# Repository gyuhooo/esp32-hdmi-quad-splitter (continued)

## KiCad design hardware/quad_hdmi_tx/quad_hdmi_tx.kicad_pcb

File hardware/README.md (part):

# 基板 (2 枚構成)

| 基板 | 内容 | 詳細 |
|---|---|---|
| `quad_hdmi_tx/` キャリア基板 rev B | ADV7513 ×4 + TPD12S016 ×4 + HDMI ×4、115 × 38 mm、6 層。裏面に 2×40 ヘッダ J7/J8 | この README |
| `fpga_main/` FPGA メイン基板 rev A | XC7A35T-1FTG256C、QSPI フラッシュ、JTAG、100 MHz、電源(5 V → 1.0 / 1.8 / 3.3 V)、115 × 72 mm、6 層。表面の 2×40 ソケット J1/J2 にキャリアを重ねる | [fpga_main/README.md](fpga_main/README.md) |

キャリア基板はメイン基板の上に重ね(基板間 約 11 mm、M3 スペーサ)、124 本の 3.3 V 信号 + GND + FPGA_5V をソケットで直結する。
両基板の KiCad プロジェクトは `gen/` のスクリプトが生成する(回路図 → ネットリスト → 配置と事前配線 → FreeRouting → DRC → ガーバー)。
FPGA のピン割り当て(`fpga_main/fpga_pinmap.csv`)から `gen/gen_xdc.py` が `constraints/board.xdc` を作る。

# Quad HDMI TX キャリア基板 (ADV7513 ×4)

FPGA メイン基板(下記 `fpga_main/`)から 24bit RGB ×4 を受け、HDMI 4 本を出す基板の KiCad 7 プロジェクト。
`gen/gen_schematic.py` が回路図・BOM・ピン割り当て表を生成し、`kicad-cli` でネットリストと PDF を書き出している。

| ファイル | 内容 |
|---|---|
| quad_hdmi_tx/quad_hdmi_tx.kicad_pro / *.kicad_sch | KiCad 7 プロジェクト(ルート + 電源 + FPGA コネクタ + HDMI OUT1〜4) |
| quad_hdmi_tx/quad_hdmi_tx.pdf | 回路図 PDF(7 ページ) |
| quad_hdmi_tx/netlist.net | kicad-cli で書き出したネットリスト |
| quad_hdmi_tx/bom.csv, bom_grouped.csv | 部品表(リファレンス別 / 集計、MPN 付き) |
| quad_hdmi_tx/fpga_header_pinmap.csv | J7/J8 のピン → 信号名 → FPGA メイン基板のボール(`gen/fpga_common.py` の割り当てで自動記入) |
| quad_hdmi_tx/quad_hdmi_tx.kicad_pcb | 基板レイアウト rev B(6 層、115 × 38 mm の細長い基板)。`gen/gen_pcb.py` が配置・プレーン・事前配線を生成し、FreeRouting で自動配線 |
| quad_hdmi_tx/drc.rpt | DRC レポート(pcbnew API) |
| quad_hdmi_tx/fab/ | ガーバー、ドリル、CPL(部品座標)、各層の PDF(`gen/export_fab.sh`) |
| quad_hdmi_tx/3d/ | STEP(基板のみ)、簡易 3D モデル(OBJ + テクスチャ)、three.js ビューア(`gen/gen_3d.py`、`gen/make_3d_textures.py`) |
| gen/ | 生成スクリプト(両基板)、ネットリスト検査、配線パイプライン。`sch_common.py`(回路図共通部)、`fpga_common.py`(FPGA のボール割り当て) |

## 回路構成

```
USB-C 5V ─ F1(PTC 2A) ─ +5V ─ U5 AP63203 (3.3V 2A buck) ─ +3V3 ─┬─ U13 TLV1117LV18 ─ CH1_1V8 ─ U11 ADV7513 ─ U12 TPD12S016 ─ J1 HDMI
                                                               ├─ U23 ...                          CH2 (I2C bus A, addr 0x7A)
                                                               ├─ U33 ...                          CH3 (I2C bus B, addr 0x72)
                                                               └─ U43 ...                          CH4 (I2C bus B, addr 0x7A)
J7 / J8 (2×40 SMD、裏面): 各チャネル 20 ピンずつ。J7 = D13-23 + D1/D2/D4/D5/D10、J8 = D0/D3/D6-9/D11/D12, CLK, DE/HS/VS, HPD, INT (+ I2C_A/I2C_B, FPGA_5V)
```

### チャネル(×4)

| 要素 | 内容 | 根拠 |
|---|---|---|
| ADV7513BSWZ (LQFP-64 EP) | 24bit RGB 4:4:4 入力 ID 0、セパレートシンク。TMDS 出力 | データシート Rev.B Table 3 のピン配置 |
| R_EXT 887 Ω 1% | TMDS 基準電流 | データシート Table 3 |
| PD/AD 10 kΩ | GND → I2C 0x72(7bit 0x39)、+3V3 → 0x7A(0x3D)。同一バス 2 台をこれで分ける | |
| INT 10 kΩ プルアップ | ヘッダへ | |
| CEC_CLK 0 Ω→GND | CEC 未使用。使う場合は 0 Ω を外して 3〜100 MHz を入れる | Table 3 |
| 未使用オーディオ入力 | SPDIF, MCLK, I2S0-3, SCLK, LRCLK を GND | |
| 電源 | DVDD ×4 / AVDD ×3 / PVDD / BGVDD = 1.8 V、DVDD_3V = 3.3 V。1.8 V はチャネルごとの LDO。AVDD と PVDD/BGVDD はフェライトビーズ経由 | 1.8 V 系は最大 256 mW/個 |
| TPD12S016PWR (TSSOP-24) | TMDS 8 本の ESD、DDC/CEC のレベルシフト(A 側 3.3 V、B 側 5 V プルアップ内蔵)、HPD、5V_OUT(55 mA リミット) | データシート SLLSE96F |
| LS_OE / CT_HPD | +3V3 固定(常時有効) | |
| HDMI A(Molex 208658-1001) | シールド、GND、SH は GND。UTILITY(14) は未接続 | |

### 電源

- USB-C(GCT USB4105-GF-A、USB2.0 16P)、CC1/CC2 に 5.1 kΩ(5 V 3 A シンク宣言)。代替 5 V 入力 J6。
- F1: PTC 2 A。+5V と VBUS に PWR_FLAG。
- U5 AP63203WU(3.3 V 固定、2 A): CIN 10 µF ×2、CBST 0.1 µF、L 4.7 µH(NR4018T4R7M)、COUT 22 µF ×2、EN は 100 kΩ で VIN へ。
- 消費見積: 1.8 V 系 4 × 142 mA ≈ 0.57 A(LDO 損失 ≈ 0.85 W、SOT-223 ×4 に分散)、3.3 V 系合計 ≈ 0.7 A、5 V 入力 ≈ 0.8 A(HDMI 5V_OUT 4 × 55 mA 含む)。
- JP1(ソルダージャンパ)を閉じると J8 の 39-40 ピン(FPGA_5V)から FPGA ボードへ 5 V を供給できる。FPGA ボードが自前電源のときは開けたままにする。

### FPGA コネクタ J7 / J8

- 2×40 ピン 2.54 mm の SMD ヘッダ 2 本を **裏面** に長辺と平行に置く(Samtec TSM-140-01-L-DV 相当)。リボンケーブル(IDC)で FPGA ボードへ。
- ヘッダの列 k(ピン 2k-1 / 2k)は OUT ⌈k/10⌉ の ADV7513 の真下にある。各チャネルは J7 で 20 ピン(ADV 左辺の D13-23 と下辺の D1/D2/D4/D5/D10、GND ×4)、J8 で 20 ピン(ADV 下辺の D0/D3/D6-9/D11、CLK, DE/HS と D12、VS, HPD, INT、GND ×4、OUT1/OUT3 は I2C、OUT2 は FPGA_5V ×2)。
  データ線の並びは配線経路(内層の通路の順序)で決めたもので、ビット順ではない。FPGA 側のピン割り当ては `fpga_header_pinmap.csv` を参照。
- GND は ADV / TPD の真下の列(J7 列 4-7 下段、J8 列 4-7 上段)に置いている(表面がふさがっていて信号のビアが打てない位置)。リボンケーブル上では 4〜9 本おき。ケーブルは 15 cm 以下を推奨(148.5 MHz SDR)。
- 3.3 V LVCMOS。FPGA ボードの該当バンクは VCCO = 3.3 V であること。
- スタック高さは 30 mm 以下を推奨(148.5 MHz SDR)。FPGA 側で 22〜33 Ω の直列終端を入れられるとなお良い。
- 相手は FPGA メイン基板 `fpga_main/` のソケット J1(= J7)/ J2(= J8)。FPGA ピンは `fpga_main/fpga_pinmap.csv` と `fpga_header_pinmap.csv` の FPGA_pin 列にあり、`python3 gen/gen_xdc.py > constraints/board.xdc` で XDC を作る。
- 市販 FPGA ボードにリボンケーブルで繋ぐ場合は `fpga_header_pinmap.csv` の FPGA_pin 列を書き換えて `gen/gen_xdc.py quad_hdmi_tx/fpga_header_pinmap.csv` を使う。

## 検証状況

| 項目 | 状態 |
|---|---|
| ADV7513 の全 65 ピン、TPD12S016 の全 24 ピンがデータシートどおりに割り当てられている | 済(スクリプトで番号を生成、検査で全ピンの接続を確認) |
| kicad-cli によるネットリスト書き出し | 済(147 部品、233 ネット) |
| ネット検査: データ線 2 ピン、TMDS 3 ピン、HPD/INT 3 ピン、I2C 4 ピン、GND/+3V3 に信号ピンが混ざっていない | 済(`gen/check_netlist.py`) |
| 基板レイアウト(配置・配線) | 済(rev B: 6 層 115 × 38 mm、配線 2010 本、ビア 634 個。HDMI・USB-C コネクタは基板端に合わせ済み) |
| DRC(pcbnew API、KiCad 7 の既定ルール + 本基板のルール) | 未接続 0、クリアランス / 穴 / 外形 / コートヤード違反 0(残りは `lib_footprint_issues` 147 件 = 生成したフットプリントがライブラリと一致しないという情報のみ) |
| TMDS 8 本 × 4 ch | ビアなし、ペア内長差 0.47 mm 以下(スクリプトで固定配線) |
| ガーバー / ドリル / CPL 出力 | 済(`quad_hdmi_tx/fab/`) |
| KiCad GUI での ERC / DRC 再確認 | **未**(GUI で開いて再実行を推奨) |
| 実機評価 | **未** |

### レイアウトの結果

| 層 | 画像 |
|---|---|
| 表面 (F.Cu) |  |
| 裏面 (B.Cu、ミラー表示) |  |
| 内層 1 (GND) |  |
| 内層 2 (SIG1) |  |
| 内層 3 (SIG2) |  |
| 内層 4 (+3V3 / CHn_1V8) |  |

TMDS の事前配線(OUT1 周辺、配線前の状態):

自動配線(FreeRouting 1.9)後の主なネット長:

```
RGB バス / 同期 (112 本): 最長 51.3 mm (D16、ヘッダ上の横レーン経由)、平均 21.4 mm、最短 4.2 mm。すべて gen_pcb.py の固定配線 (ビア 1〜2 個)
I2C_A_SCL 70 mm (OUT1/OUT2 の ADV とプルアップ、J8 経由)、I2C_B_SCL 56 mm
HPD 20 mm、INT 25 mm、DDC_SCL / CEC 15 mm (TPD -> HDMI)、FPGA_5V 72 mm (J8 ピン 39/40 -> JP1)
+5V 197 mm (ビア 9)、+3V3 132 mm (ビア 41、内層 4 のプレーンが主)、GND 326 mm (ビア 203、内層 1 のプレーンが主)
TMDS: ペア内長差 0.05〜0.47 mm、ビアなし
```

### 3D モデル

| 表 | 裏 |
|---|---|
|  |  |

`quad_hdmi_tx/3d/` に 3 種類ある(`gen/gen_3d.py` と `gen/make_3d_textures.py` で生成):

| ファイル | 内容 |
|---|---|
| `quad_hdmi_tx.step` | kicad-cli の STEP 出力。この環境には KiCad の 3D モデルライブラリが無いため **基板のみ**(部品なし)。筐体設計の基準に使える |
| `quad_hdmi_tx_simplified.obj` / `.mtl` / `tex_top.png` / `tex_bot.png` | 簡易モデル(Wavefront OBJ、mm、Y 上)。基板は表裏にレジスト・金パッド・シルクのテクスチャ、部品はパッケージ種別の寸法表による直方体(IC・受動部品・コネクタ・ヘッダのピン) |
| `viewer.html` | 上の簡易モデルを three.js で回転表示する 1 ファイルのビューア(ブラウザで開く) |

部品の外形は寸法表の近似なので、正確な 3D モデルが要るときは KiCad の 3D ライブラリを入れて `kicad-cli pcb export step` を再実行する。

## 発注前チェックリスト

1. **ADV7513 の推奨回路**: ハードウェアユーザーガイド(ADI)で、PVDD/BGVDD のフィルタ構成と HPD/DDC の扱いが本回路(フェライトビーズ + 0.1 µF、TPD12S016 経由)と矛盾しないか確認する。
2. **フットプリント**: ADV7513 の露出パッドは 5.3 mm 角。`LQFP-64-1EP_10x10mm_P0.5mm_EP5x5mm` を使い、EP のサーマルビア(0.5/0.3 mm ×14)は裏面ヘッダのパッドを避けて `gen_pcb.py` が打っている。
3. **HDMI コネクタ**: Molex 208658-1001 の KiCad 標準フットプリント。別品番なら 1〜19 + シェルの配列を照合する。
4. **USB-C**: GCT USB4105-GF-A の標準フットプリント。NPTH と自身のパッドの間隔が 0.194 mm なので、穴クリアランスの規則を 0.18 mm にしている。
5. **LDO**: TLV1117LV18DCYR(セラミック出力対応、1 A)。AMS1117-1.8 はピン互換だがタンタル出力推奨。
6. **I2C アドレス**: 同一バスに 2 台(0x72 と 0x7A)。HDL の `top.v` はバス 0 = OUT1/OUT2、バス 1 = OUT3/OUT4 でこの割り当てを前提にしている。
7. **KiCad GUI で ERC と DRC を再実行する**: 本リポジトリの検査は pcbnew API のレポート。DRC の残り 143 件は「フットプリントがライブラリと一致しない」情報(ライブラリ名なしで読み込んだため)で、製造には影響しない。
8. **インピーダンス**: TMDS は 0.15 mm 幅 / 0.15 mm 間隔で固定配線している。製造業者の 6 層スタックアップ(例: JLC06161H-3313、F.Cu〜In1 が 0.1 mm 程度)の計算値に合わせて幅・間隔を調整し、必要なら `gen/gen_pcb.py` のネットクラスと事前配線幅を変えて再生成する。
9. **自動配線部の目視確認**: RGB バス(148.5 MHz)30 本は `gen_pcb.py` の固定配線(内層 SIG1/SIG2、各線 40 mm 以下)。電源・I2C・CEC・HPD 系は FreeRouting の結果なので、ADV 右辺付近の AVDD/PVDD と I2C の引き回しをレビューし、必要なら手で整える。
10. **シルク**: 参照記号は F.Fab に置いている(シルクには出ない)。実装は `fab/cpl.csv` の座標で行う。
11. **コネクタの基板端合わせ**: HDMI(Molex 208658)と USB-C(GCT USB4105)のフットプリントには "PCB Edge" の基準線がある。
    生成スクリプトはこの線が基板外形(HDMI: y=0、USB-C: x=115)に一致するよう配置している(HDMI は本体が 1.5 mm、USB-C は 0.5 mm 外形からはみ出す)。
    ケースに入れる場合はこのはみ出し量を前提に開口を設計する。
12. **裏面のヘッダと IDC ソケット**: J7/J8 の中心間隔は 15.4 mm、J8 は下辺から 4.4 mm。IDC ソケット(幅 8.9 mm)は J8 側が基板端とほぼ面一になる。基板の下に高さ 10 mm 以上の空間が必要。
13. **両面実装**: LDO ×4、そのコンデンサ、ヘッダ 2 本、JP1 が裏面。実装業者には両面(F+B)の CPL を渡す。裏面の SMD ヘッダはリフロー可能品(TSM-140-01-L-DV 等)を選ぶ。
14. **取付穴**: M3 ×4(HDMI の間に 3 個、右下に 1 個)。HDMI の間の穴はプラグのオーバーモールド(幅 ~21 mm)と干渉しない位置だが、ナットは基板の裏側に置くこと。

## 基板レイアウト

### 配置(rev B: 115 × 38 mm、縦横比 0.33)

```
 y=0  ┌───────────────────────────────────────────────────────────────────────┐
      │ [J1 HDMI] H1 [J2 HDMI]  H2 [J3 HDMI]  H4 [J4 HDMI]   R5 R6 F1  [J5]   │  上辺: HDMI ×4 (25.4 mm ピッチ、開口部は上)。裏面の真裏に LDO
      │  U12 TPD     U22 TPD       U32 TPD       U42 TPD      C54     USB-C   │  TPD12S016 (rot 90)。両脇に +3V3 / 5V 系のコンデンサ
      │  U11 ADV     U21 ADV       U31 ADV       U41 ADV      U5  C51  L1     │  ADV7513 (rot 180)。左右の列に 1V8 / AVDD / PVDD 系
      │                                                      C52 C53  C55 C56 │  電源部 (右端)
 y=38 └───────────────────────────────────────────────────────────────────────┘
        x=0                              裏面: J7 (y=18.2) と J8 (y=33.6) が x=1.6..101.6 に横たわる        x=115

 裏面 (透視): [LDO U13][LDO U23][LDO U33][LDO U43] ← HDMI のシェルタブの穴の間
             ═══════════ J7 2×40 (列 1-10 = OUT1, 11-20 = OUT2, 21-30 = OUT3, 31-40 = OUT4) ═══════════
             ═══════════ J8 2×40 (同じ列割り) ═══════════════════════════════════════════════════  JP1
```

- HDMI 4 個の横幅(4 × 25.4 mm)に電源部を足した 115 mm を横幅とし、縦幅は 38 mm(横の 1/3 以下)。
- 各チャネルは幅 25.4 mm = ヘッダ 10 列。ヘッダの列は ADV の真下なので、RGB バスの配線は 1 本あたり 15 mm 以下。
- TMDS の並び順が ADV7513(rot 180)→ TPD12S016(rot 90)→ HDMI(rot 90)で **交差なし**に揃うよう向きを決めている
  (ADV 上辺: TX2+ TX2- TX1+ TX1- TX0+ TX0- TXC+ TXC-、TPD 上辺: D2+ D2- D1+ D1- D0+ D0- CLK+ CLK-、コネクタ: 1 3 4 6 7 9 10 12)。
- 裏面ヘッダのパッド(1.0 mm 幅、2.54 mm ピッチ)の隙間は 1.54 mm しかないので、貫通ビアはパッド列の隙間の中心(x = cx ± 2.54 m)か、
  2 列の間 / J7-J8 の間の帯に置く。2 端子部品はすべて縦置きでこの x に載せ、外向きのビアが隙間に来るようにしている。
  TPD の A 側ピンのビア(y = 18.3 / 18.7)は J7 の 2 列の隙間(y 17.25〜19.15)に、ADV 上辺の囲われたピンのビア(y = 26.0 / 26.6)は J7-J8 の間の帯に入る。
- ADV のデータピンはルータ任せでは半分が配線できない(裏面ヘッダのパッドが B.Cu を塞ぐ)ので、`gen_pcb.py` が 30 本の RGB/同期/制御線をすべて事前配線する(残りの電源・I2C・CEC などが FreeRouting):
  - 下辺 16 ピンのエスケープビアは本体下(EP とパッド内端の間 = J8 の 2 列の隙間に当たる y)に 2 段。真下の J8 下段 4 本(D11/D8/D3/HS)は裏面で直落とし、
    D6/D7/CLK/D9 と DE/D0 は SIG2 の横レーン(y = 34.8〜36.5)で J8 列 1-2 / 列 9 の隙間ビアへ、D1/D2/D4/D5/D10 は ADV 右脇の通路(x = cx+3.35/3.65/3.95)を上って J7 列 8-10 へ。
  - 左辺 16 ピンは左へ(上 5 本は x=cx-7.0/-7.62 に交互、中 8 本は隙間の列 x=cx-7.62 に 0.65 ピッチで斜めに、D14/D13 は本体下、D12 は隙間の列の一番下)。
    D16-D23 と DDC は左の内層通路(x = cx-8.19〜-9.69、SIG1/SIG2 各 6 レーン)を上り、J7 列 1-2 の隙間ビア、またはヘッダの上(y = 11.5〜12.1)の横レーン経由で列 5-8 上段へ。
    D13/D14/D15 は ADV 脇の帯(x = cx-6.5〜-5.5)を SIG2 で上って列 3-4 へ。J8 列 4-7 上段(GND)は EP のサーマルビアに裏面で直結。
  - レーンの割り当ては「右の通路ほど低い横レーン」「横レーンから下に曲がる先は左ほど低いレーン」の規則で決め、事前配線どうしが交差しないようにしている。
  - そのほか、ルータが落としやすい DDC_SCL(TPD → HDMI、SIG2 で右上へ抜けて表面でコネクタの上を回る)と FPGA_5V(J8 ピン 39/40 → JP1、SIG2 で基板下端を右へ)も固定配線。
- LDO(SOT-223)は HDMI コネクタの真裏、シェルタブの穴の間。出力は裏面の太い配線で内層 4 の 1V8 の島の「首」へ入る。
- 電源部は右端(USB-C の開口部は右)。

### 層構成(6 層、1.6 mm)

| 層 | 用途 |
|---|---|
| F.Cu | 信号(TMDS 事前配線、短い引き出し)、部品 |
| In1.Cu (GND) | GND プレーン(全面) |
| In2.Cu (SIG1) / In3.Cu (SIG2) | 信号(RGB バス、制御線、+5V) |
| In4.Cu (PWR) | +3V3 プレーン。各 ADV の周囲は CHn_1V8 の島(優先度 1)。島は LDO へ向けて首を伸ばしている |
| B.Cu | FPGA ヘッダ、LDO、信号、配線後に GND ベタ |

4 層では裏面ヘッダのパッド列が B.Cu を塞ぐため、RGB バスの配線が成立しない。6 層にして内層 2 層を信号に使う。

### ルール

| 項目 | 値 |
|---|---|
| クリアランス | 0.15 mm |
| 配線幅 | 0.2 mm(TMDS 0.15、Power 0.5) |
| ビア | 0.6/0.3 mm(TMDS・アクセスビア 0.5/0.3、Power 0.8/0.4) |
| 差動 | 100 Ω 目標、0.15/0.15 mm(**製造業者のインピーダンス計算で要調整**) |

### 生成と配線のパイプライン

```
cd hardware/gen
python3 gen_pcb.py                       # 配置・外形・プレーン・事前配線・ファンアウト -> quad_hdmi_tx.kicad_pcb, drc_pre.rpt
python3 route_pcb.py export              # quad_hdmi_tx.dsn
xvfb-run -a java -jar freerouting-1.9.0.jar -de ../quad_hdmi_tx/quad_hdmi_tx.dsn -do ../quad_hdmi_tx/quad_hdmi_tx.ses -mp 24 -oit 1.0   # 約 10 分
python3 route_pcb.py import              # SES 取り込み、外層 GND ベタ、ゾーン塗り、DRC -> drc.rpt
python3 layout_report.py                 # 配線長、ビア数、TMDS ペア長差、DRC 集計
./export_fab.sh                          # fab/ にガーバー・ドリル・CPL・PDF
python3 render_images.py                 # fab/*.pdf → docs/images/pcb-*.png (Pillow, pdftoppm)
python3 gen_3d.py                        # 3d/board3d.json, 簡易 OBJ/MTL (pcbnew)
python make_3d_textures.py               # 3d/tex_*.png と 3d/viewer.html (Pillow + numpy。先に各層の白黒 PDF→PNG が要る、スクリプト冒頭参照)
```

FreeRouting を使う上での注意(実測で判明したもの):

- 外層のベタを DSN に含めると障害物として扱われ配線できないため、ベタは SES 取り込み後に追加している。
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
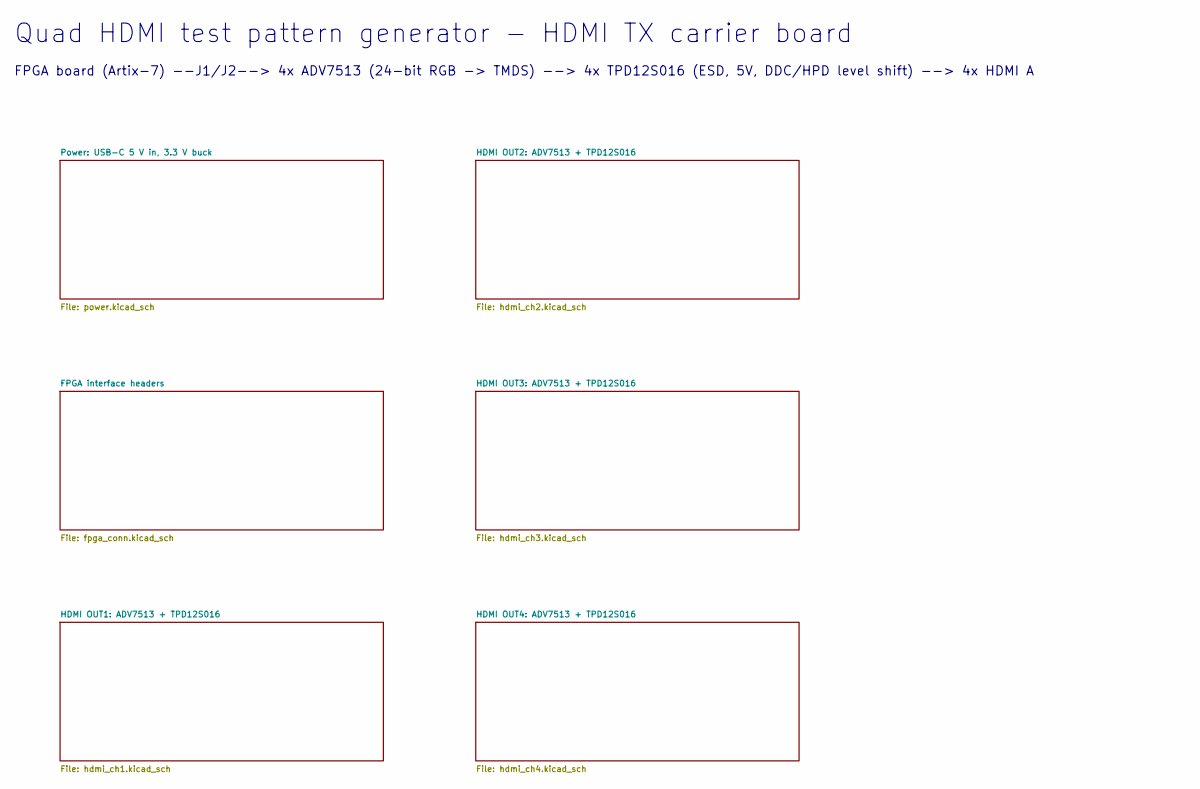
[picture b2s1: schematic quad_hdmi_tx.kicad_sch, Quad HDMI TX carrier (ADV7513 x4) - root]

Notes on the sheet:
Quad HDMI test pattern generator - HDMI TX carrier board
FPGA board (Artix-7) --J1/J2--> 4x ADV7513 (24-bit RGB -> TMDS) --> 4x TPD12S016 (ESD, 5V, DDC/HPD level shift) --> 4x HDMI A

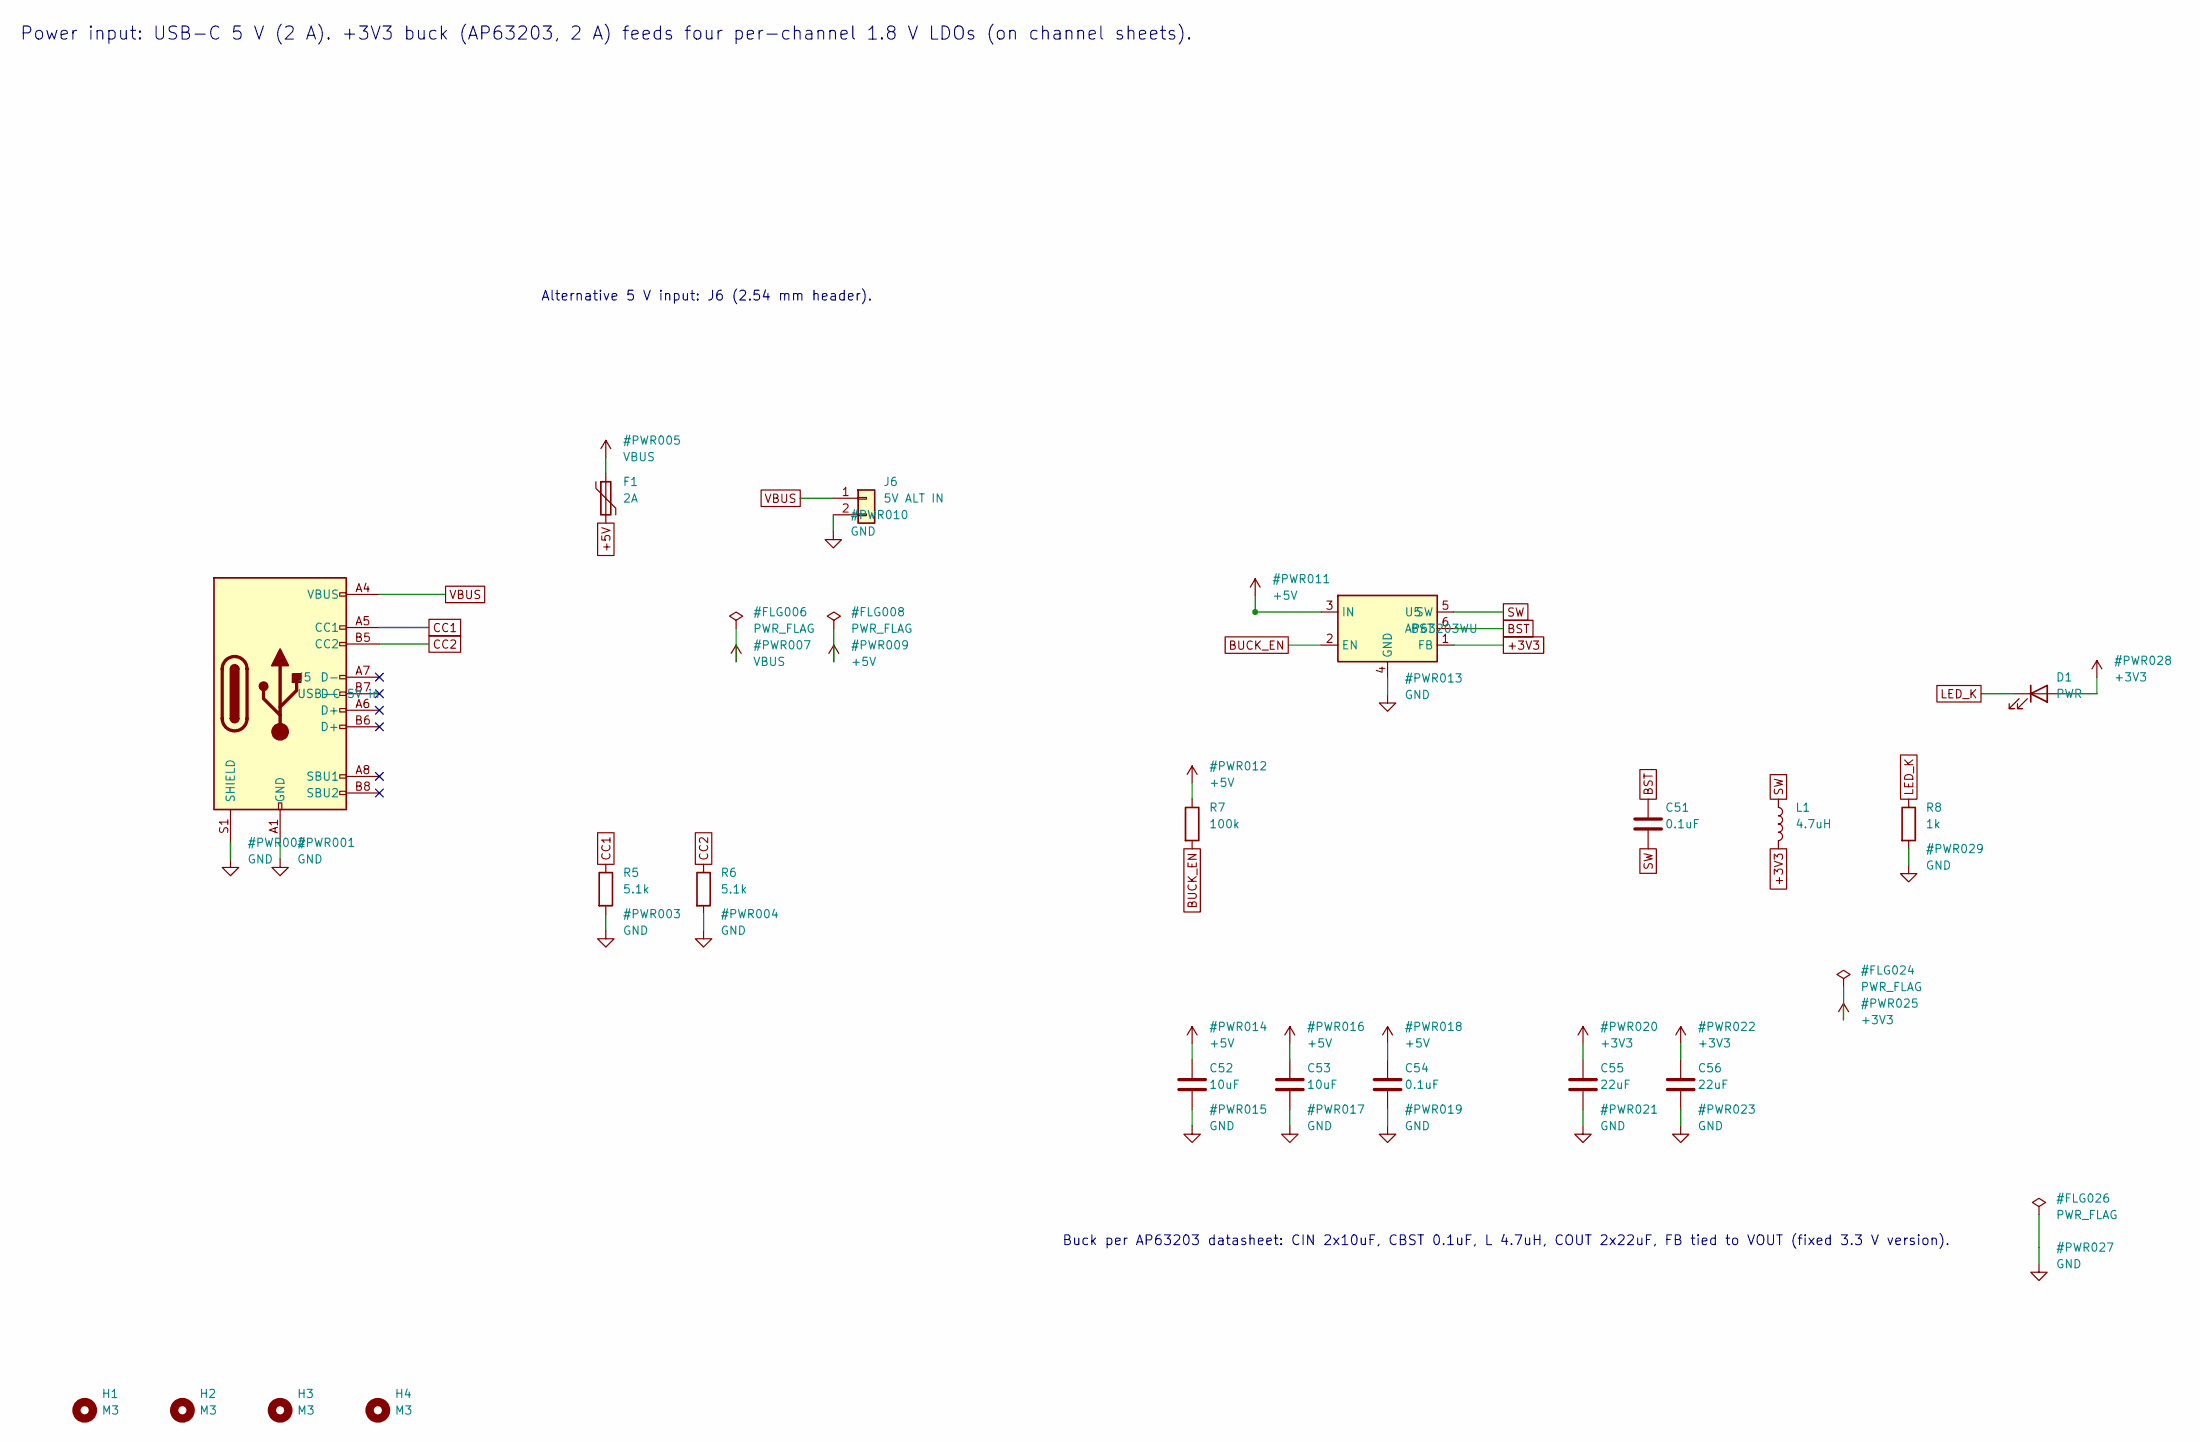
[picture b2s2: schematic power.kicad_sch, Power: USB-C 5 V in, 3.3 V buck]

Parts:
C51, C54: 0.1uF; C_0402_1005Metric; MPN GRM155R71C104KA88D
C52, C53: 10uF; C_0805_2012Metric; MPN GRM21BR61A106KE19L
C55, C56: 22uF; C_0805_2012Metric; MPN GRM21BR60J226ME39L
D1: PWR; LED_0603_1608Metric; MPN LTST-C193KGKT-5A
F1: 2A; Fuse_1206_3216Metric; MPN 1206L200/12SLYR
H1, H2, H3, H4: M3; MountingHole_3.2mm
J5: USB-C 5V in; USB_C_Receptacle_GCT_USB4105-xx-A_16P_TopMnt_Horizontal; MPN USB4105-GF-A
J6: 5V ALT IN; PinHeader_1x02_P2.54mm_Vertical
L1: 4.7uH; L_Taiyo-Yuden_NR-40xx; MPN NR4018T4R7M
R5, R6: 5.1k; R_0402_1005Metric; MPN RC0402FR-075K1L
R7: 100k; R_0402_1005Metric; MPN RC0402FR-07100KL
R8: 1k; R_0402_1005Metric; MPN RC0402FR-071KL
U5: AP63203WU; TSOT-23-6; MPN AP63203WU-7

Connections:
+3V3: C55.1, C56.1, D1.2 (A), L1.2, U5.1 (FB); also elsewhere on the board
+5V: C52.1, C53.1, C54.1, F1.2, R7.1, U5.3 (IN); also elsewhere on the board
BST: C51.1, U5.6 (BST)
BUCK_EN: R7.2, U5.2 (EN)
CC1: J5.A5 (CC1), R5.1
CC2: J5.B5 (CC2), R6.1
GND: C52.2, C53.2, C54.2, C55.2, C56.2, J5.A1 (GND), J5.A12 (GND), J5.B1 (GND), J5.B12 (GND), J5.S1 (SHIELD), J6.2, R5.2, R6.2, R8.2, U5.4 (GND); also elsewhere on the board
LED_K: D1.1 (K), R8.1
SW: C51.2, L1.1, U5.5 (SW)
VBUS: F1.1, J5.A4 (VBUS), J5.A9 (VBUS), J5.B4 (VBUS), J5.B9 (VBUS), J6.1

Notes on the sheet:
Power input: USB-C 5 V (2 A). +3V3 buck (AP63203, 2 A) feeds four per-channel 1.8 V LDOs (on channel sheets).
Alternative 5 V input: J6 (2.54 mm header).
Buck per AP63203 datasheet: CIN 2x10uF, CBST 0.1uF, L 4.7uH, COUT 2x22uF, FB tied to VOUT (fixed 3.3 V version).

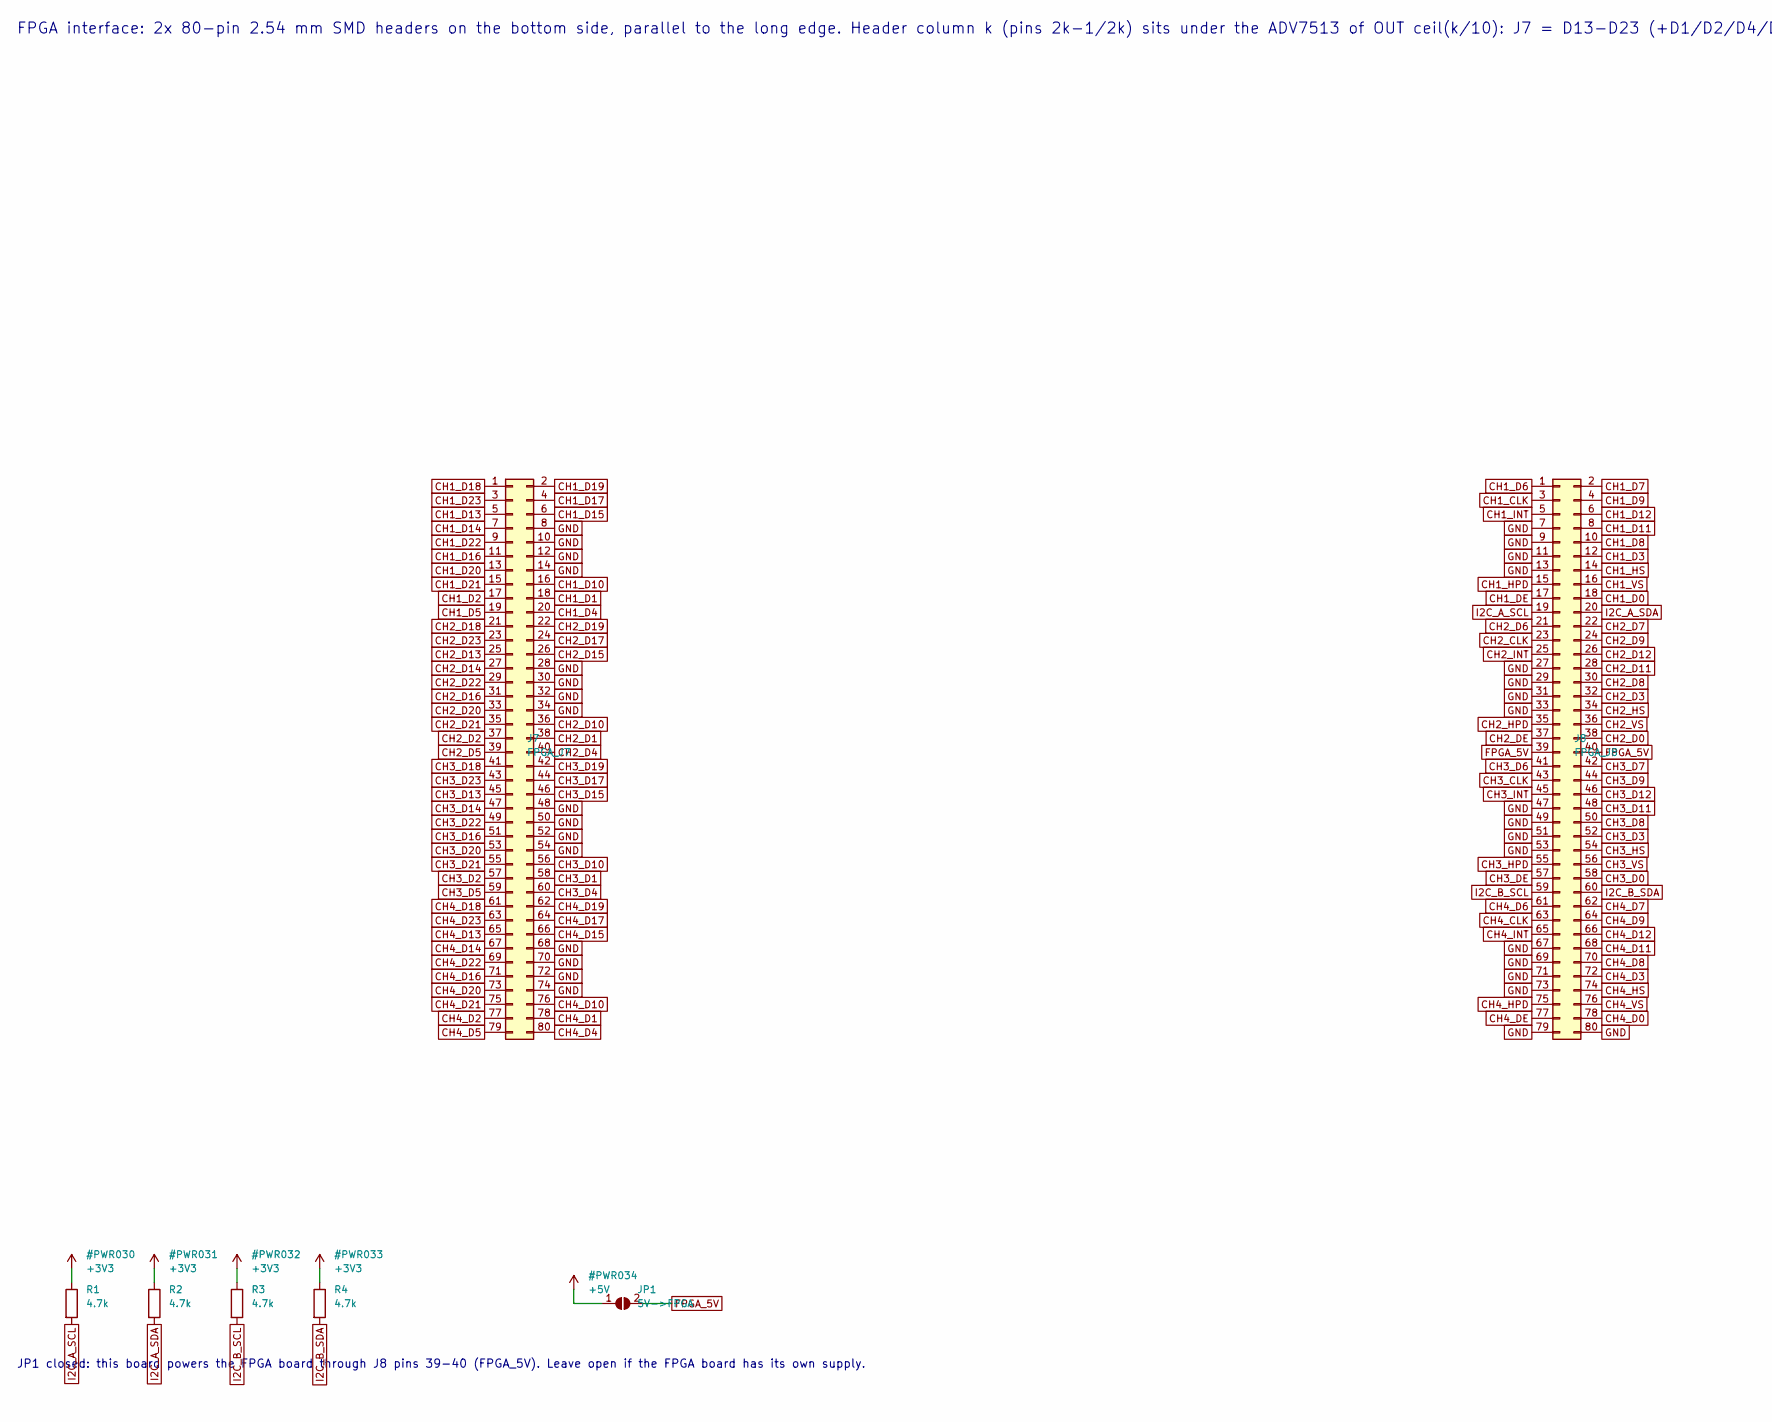
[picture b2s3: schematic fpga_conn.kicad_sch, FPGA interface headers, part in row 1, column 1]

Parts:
J7: FPGA_J7; PinHeader_2x40_P2.54mm_Vertical_SMD; MPN TSM-140-01-L-DV
J8: FPGA_J8; PinHeader_2x40_P2.54mm_Vertical_SMD; MPN TSM-140-01-L-DV
JP1: 5V->FPGA; SolderJumper-2_P1.3mm_Open_RoundedPad1.0x1.5mm
R1, R2, R3, R4: 4.7k; R_0402_1005Metric; MPN RC0402FR-074K7L

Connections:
+3V3: R1.1, R2.1, R3.1, R4.1; also elsewhere on the board
+5V: JP1.1 (A); also elsewhere on the board
CH1_CLK: J8.3; also elsewhere on the board
CH1_D0: J8.18; also elsewhere on the board
CH1_D1: J7.18; also elsewhere on the board
CH1_D2: J7.17; also elsewhere on the board
CH1_D3: J8.12; also elsewhere on the board
CH1_D4: J7.20; also elsewhere on the board
CH1_D5: J7.19; also elsewhere on the board
CH1_D6: J8.1; also elsewhere on the board
CH1_D7: J8.2; also elsewhere on the board
CH1_D8: J8.10; also elsewhere on the board
CH1_D9: J8.4; also elsewhere on the board
CH1_D10: J7.16; also elsewhere on the board
CH1_D11: J8.8; also elsewhere on the board
CH1_D12: J8.6; also elsewhere on the board
CH1_D13: J7.5; also elsewhere on the board
CH1_D14: J7.7; also elsewhere on the board
CH1_D15: J7.6; also elsewhere on the board
CH1_D16: J7.11; also elsewhere on the board
CH1_D17: J7.4; also elsewhere on the board
CH1_D18: J7.1; also elsewhere on the board
CH1_D19: J7.2; also elsewhere on the board
CH1_D20: J7.13; also elsewhere on the board
CH1_D21: J7.15; also elsewhere on the board
CH1_D22: J7.9; also elsewhere on the board
CH1_D23: J7.3; also elsewhere on the board
CH1_DE: J8.17; also elsewhere on the board
CH1_HPD: J8.15; also elsewhere on the board
CH1_HS: J8.14; also elsewhere on the board
CH1_INT: J8.5; also elsewhere on the board
CH1_VS: J8.16; also elsewhere on the board
CH2_CLK: J8.23; also elsewhere on the board
CH2_D0: J8.38; also elsewhere on the board
CH2_D1: J7.38; also elsewhere on the board
CH2_D2: J7.37; also elsewhere on the board
CH2_D3: J8.32; also elsewhere on the board
CH2_D4: J7.40; also elsewhere on the board
CH2_D5: J7.39; also elsewhere on the board
CH2_D6: J8.21; also elsewhere on the board
CH2_D7: J8.22; also elsewhere on the board
CH2_D8: J8.30; also elsewhere on the board
CH2_D9: J8.24; also elsewhere on the board
CH2_D10: J7.36; also elsewhere on the board
CH2_D11: J8.28; also elsewhere on the board
CH2_D12: J8.26; also elsewhere on the board
CH2_D13: J7.25; also elsewhere on the board
CH2_D14: J7.27; also elsewhere on the board
CH2_D15: J7.26; also elsewhere on the board
CH2_D16: J7.31; also elsewhere on the board
CH2_D17: J7.24; also elsewhere on the board
CH2_D18: J7.21; also elsewhere on the board
CH2_D19: J7.22; also elsewhere on the board
CH2_D20: J7.33; also elsewhere on the board
CH2_D21: J7.35; also elsewhere on the board
CH2_D22: J7.29; also elsewhere on the board
CH2_D23: J7.23; also elsewhere on the board
CH2_DE: J8.37; also elsewhere on the board
CH2_HPD: J8.35; also elsewhere on the board
CH2_HS: J8.34; also elsewhere on the board
CH2_INT: J8.25; also elsewhere on the board
CH2_VS: J8.36; also elsewhere on the board
CH3_CLK: J8.43; also elsewhere on the board
CH3_D0: J8.58; also elsewhere on the board
CH3_D1: J7.58; also elsewhere on the board
CH3_D2: J7.57; also elsewhere on the board
CH3_D3: J8.52; also elsewhere on the board
CH3_D4: J7.60; also elsewhere on the board
CH3_D5: J7.59; also elsewhere on the board
CH3_D6: J8.41; also elsewhere on the board
CH3_D7: J8.42; also elsewhere on the board
CH3_D8: J8.50; also elsewhere on the board
CH3_D9: J8.44; also elsewhere on the board
CH3_D10: J7.56; also elsewhere on the board
CH3_D11: J8.48; also elsewhere on the board
CH3_D12: J8.46; also elsewhere on the board
CH3_D13: J7.45; also elsewhere on the board
CH3_D14: J7.47; also elsewhere on the board
CH3_D15: J7.46; also elsewhere on the board
CH3_D16: J7.51; also elsewhere on the board
CH3_D17: J7.44; also elsewhere on the board
CH3_D18: J7.41; also elsewhere on the board
CH3_D19: J7.42; also elsewhere on the board
CH3_D20: J7.53; also elsewhere on the board
CH3_D21: J7.55; also elsewhere on the board
CH3_D22: J7.49; also elsewhere on the board
CH3_D23: J7.43; also elsewhere on the board
CH3_DE: J8.57; also elsewhere on the board
CH3_HPD: J8.55; also elsewhere on the board
CH3_HS: J8.54; also elsewhere on the board
CH3_INT: J8.45; also elsewhere on the board
CH3_VS: J8.56; also elsewhere on the board
CH4_CLK: J8.63; also elsewhere on the board
CH4_D0: J8.78; also elsewhere on the board
CH4_D1: J7.78; also elsewhere on the board
CH4_D2: J7.77; also elsewhere on the board
CH4_D3: J8.72; also elsewhere on the board
CH4_D4: J7.80; also elsewhere on the board
CH4_D5: J7.79; also elsewhere on the board
CH4_D6: J8.61; also elsewhere on the board
CH4_D7: J8.62; also elsewhere on the board
CH4_D8: J8.70; also elsewhere on the board
CH4_D9: J8.64; also elsewhere on the board
CH4_D10: J7.76; also elsewhere on the board
CH4_D11: J8.68; also elsewhere on the board
CH4_D12: J8.66; also elsewhere on the board
CH4_D13: J7.65; also elsewhere on the board
CH4_D14: J7.67; also elsewhere on the board
CH4_D15: J7.66; also elsewhere on the board
CH4_D16: J7.71; also elsewhere on the board
CH4_D17: J7.64; also elsewhere on the board
CH4_D18: J7.61; also elsewhere on the board
CH4_D19: J7.62; also elsewhere on the board
CH4_D20: J7.73; also elsewhere on the board
CH4_D21: J7.75; also elsewhere on the board
CH4_D22: J7.69; also elsewhere on the board
CH4_D23: J7.63; also elsewhere on the board
CH4_DE: J8.77; also elsewhere on the board
CH4_HPD: J8.75; also elsewhere on the board
CH4_HS: J8.74; also elsewhere on the board
CH4_INT: J8.65; also elsewhere on the board
CH4_VS: J8.76; also elsewhere on the board
FPGA_5V: J8.39, J8.40, JP1.2 (B)
GND: J7.8, J7.10, J7.12, J7.14, J7.28, J7.30, J7.32, J7.34, J7.48, J7.50, J7.52, J7.54, J7.68, J7.70, J7.72, J7.74, J8.7, J8.9, J8.11, J8.13, J8.27, J8.29, J8.31, J8.33, J8.47, J8.49, J8.51, J8.53, J8.67, J8.69, J8.71, J8.73, J8.79, J8.80; also elsewhere on the board
I2C_A_SCL: J8.19, R1.2; also elsewhere on the board
I2C_A_SDA: J8.20, R2.2; also elsewhere on the board
I2C_B_SCL: J8.59, R3.2; also elsewhere on the board
I2C_B_SDA: J8.60, R4.2; also elsewhere on the board

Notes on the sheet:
FPGA interface: 2x 80-pin 2.54 mm SMD headers on the bottom side, parallel to the long edge. Header column k (pins 2k-1/2k) sits under the ADV7513 of OUT ceil(k/10): J7 = D13-D23 (+D1/D2/D4/D5/D10), J8 = D0-D9/D11/D12/CLK/DE/HS/VS/HPD/INT (+I2C, 5V). 3.3 V LVCMOS, 148.5 MHz SDR: keep ribbon cables 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
JP1 closed: this board powers the FPGA board through J8 pins 39-40 (FPGA_5V). Leave open if the FPGA board has its own supply.

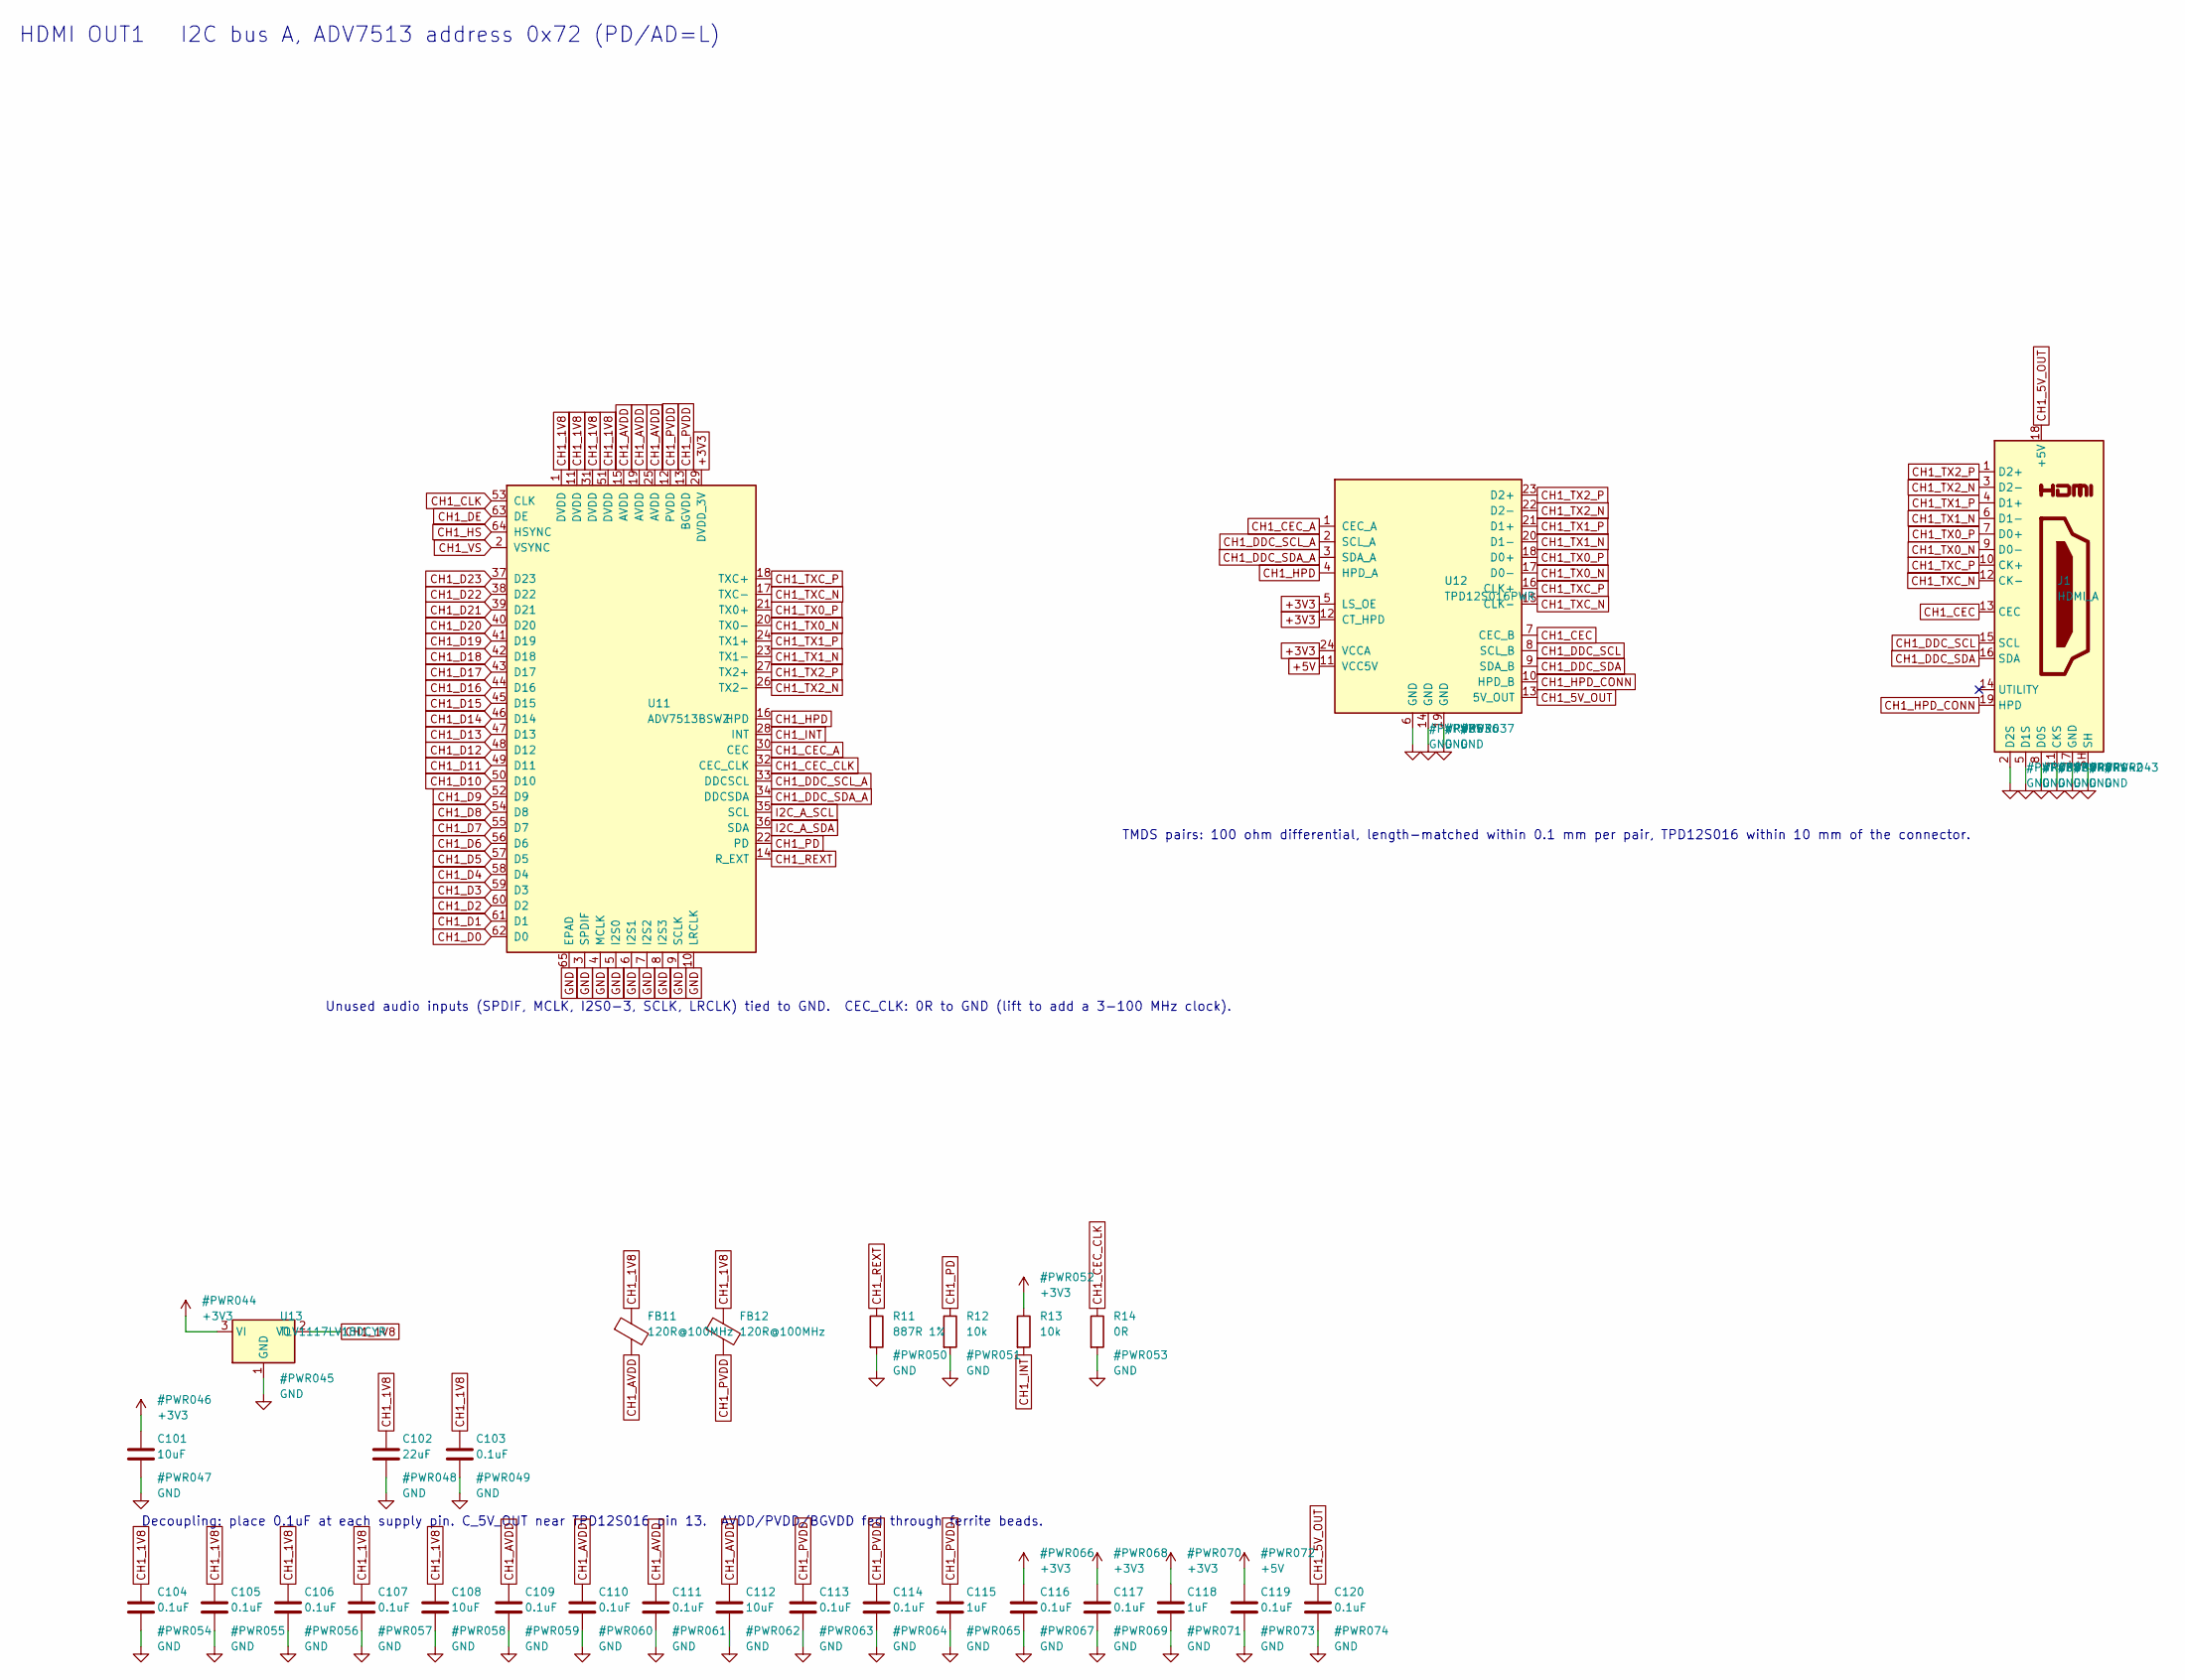
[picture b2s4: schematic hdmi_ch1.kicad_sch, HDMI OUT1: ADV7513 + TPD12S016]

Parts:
C101, C108, C112: 10uF; C_0603_1608Metric; MPN GRM188R60J106ME47D
C102: 22uF; C_0805_2012Metric; MPN GRM21BR60J226ME39L
C103, C104, C105, C106, C107, C109, C110, C111, C113, C114, C116, C117, C119, C120: 0.1uF; C_0402_1005Metric; MPN GRM155R71C104KA88D
C115, C118: 1uF; C_0603_1608Metric; MPN GRM188R61A105KA61D
FB11, FB12: 120R@100MHz; L_0603_1608Metric; MPN BLM18PG121SN1D
J1: HDMI_A; HDMI_A_Molex_208658-1001_Horizontal; MPN 208658-1001
R11: 887R 1%; R_0402_1005Metric; MPN RC0402FR-07887RL
R12, R13: 10k; R_0402_1005Metric; MPN RC0402FR-0710KL
R14: 0R; R_0402_1005Metric; MPN RC0402FR-070RL
U11: ADV7513BSWZ; LQFP-64-1EP_10x10mm_P0.5mm_EP5x5mm; MPN ADV7513BSWZ
U12: TPD12S016PWR; TSSOP-24_4.4x7.8mm_P0.65mm; MPN TPD12S016PWR
U13: TLV1117LV18DCYR; SOT-223-3_TabPin2; MPN TLV1117LV18DCYR

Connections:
+3V3: C101.1, C116.1, C117.1, C118.1, R13.1, U11.29 (DVDD_3V), U12.5 (LS_OE), U12.12 (CT_HPD), U12.24 (VCCA), U13.3 (VI); also elsewhere on the board
+5V: C119.1, U12.11 (VCC5V); also elsewhere on the board
CH1_1V8: C102.1, C103.1, C104.1, C105.1, C106.1, C107.1, C108.1, FB11.1, FB12.1, U11.1 (DVDD), U11.11 (DVDD), U11.31 (DVDD), U11.51 (DVDD), U13.2 (VO)
CH1_5V_OUT: C120.1, J1.18 (+5V), U12.13 (5V_OUT)
CH1_AVDD: C109.1, C110.1, C111.1, C112.1, FB11.2, U11.15 (AVDD), U11.19 (AVDD), U11.25 (AVDD)
CH1_CEC: J1.13 (CEC), U12.7 (CEC_B)
CH1_CEC_A: U11.30 (CEC), U12.1 (CEC_A)
CH1_CEC_CLK: R14.1, U11.32 (CEC_CLK)
CH1_CLK: U11.53 (CLK); also elsewhere on the board
CH1_D0: U11.62 (D0); also elsewhere on the board
CH1_D1: U11.61 (D1); also elsewhere on the board
CH1_D2: U11.60 (D2); also elsewhere on the board
CH1_D3: U11.59 (D3); also elsewhere on the board
CH1_D4: U11.58 (D4); also elsewhere on the board
CH1_D5: U11.57 (D5); also elsewhere on the board
CH1_D6: U11.56 (D6); also elsewhere on the board
CH1_D7: U11.55 (D7); also elsewhere on the board
CH1_D8: U11.54 (D8); also elsewhere on the board
CH1_D9: U11.52 (D9); also elsewhere on the board
CH1_D10: U11.50 (D10); also elsewhere on the board
CH1_D11: U11.49 (D11); also elsewhere on the board
CH1_D12: U11.48 (D12); also elsewhere on the board
CH1_D13: U11.47 (D13); also elsewhere on the board
CH1_D14: U11.46 (D14); also elsewhere on the board
CH1_D15: U11.45 (D15); also elsewhere on the board
CH1_D16: U11.44 (D16); also elsewhere on the board
CH1_D17: U11.43 (D17); also elsewhere on the board
CH1_D18: U11.42 (D18); also elsewhere on the board
CH1_D19: U11.41 (D19); also elsewhere on the board
CH1_D20: U11.40 (D20); also elsewhere on the board
CH1_D21: U11.39 (D21); also elsewhere on the board
CH1_D22: U11.38 (D22); also elsewhere on the board
CH1_D23: U11.37 (D23); also elsewhere on the board
CH1_DDC_SCL: J1.15 (SCL), U12.8 (SCL_B)
CH1_DDC_SCL_A: U11.33 (DDCSCL), U12.2 (SCL_A)
CH1_DDC_SDA: J1.16 (SDA), U12.9 (SDA_B)
CH1_DDC_SDA_A: U11.34 (DDCSDA), U12.3 (SDA_A)
CH1_DE: U11.63 (DE); also elsewhere on the board
CH1_HPD: U11.16 (HPD), U12.4 (HPD_A); also elsewhere on the board
CH1_HPD_CONN: J1.19 (HPD), U12.10 (HPD_B)
CH1_HS: U11.64 (HSYNC); also elsewhere on the board
CH1_INT: R13.2, U11.28 (INT); also elsewhere on the board
CH1_PD: R12.1, U11.22 (PD)
CH1_PVDD: C113.1, C114.1, C115.1, FB12.2, U11.12 (PVDD), U11.13 (BGVDD)
CH1_REXT: R11.1, U11.14 (R_EXT)
CH1_TX0_N: J1.9 (D0-), U11.20 (TX0-), U12.17 (D0-)
CH1_TX0_P: J1.7 (D0+), U11.21 (TX0+), U12.18 (D0+)
CH1_TX1_N: J1.6 (D1-), U11.23 (TX1-), U12.20 (D1-)
CH1_TX1_P: J1.4 (D1+), U11.24 (TX1+), U12.21 (D1+)
CH1_TX2_N: J1.3 (D2-), U11.26 (TX2-), U12.22 (D2-)
CH1_TX2_P: J1.1 (D2+), U11.27 (TX2+), U12.23 (D2+)
CH1_TXC_N: J1.12 (CK-), U11.17 (TXC-), U12.15 (CLK-)
CH1_TXC_P: J1.10 (CK+), U11.18 (TXC+), U12.16 (CLK+)
CH1_VS: U11.2 (VSYNC); also elsewhere on the board
GND: C101.2, C102.2, C103.2, C104.2, C105.2, C106.2, C107.2, C108.2, C109.2, C110.2, C111.2, C112.2, C113.2, C114.2, C115.2, C116.2, C117.2, C118.2, C119.2, C120.2, J1.2 (D2S), J1.5 (D1S), J1.8 (D0S), J1.11 (CKS), J1.17 (GND), J1.SH, R11.2, R12.2, R14.2, U11.3 (SPDIF), U11.4 (MCLK), U11.5 (I2S0), U11.6 (I2S1), U11.7 (I2S2), U11.8 (I2S3), U11.9 (SCLK), U11.10 (LRCLK), U11.65 (EPAD), U12.6 (GND), U12.14 (GND), U12.19 (GND), U13.1 (GND); also elsewhere on the board
I2C_A_SCL: U11.35 (SCL); also elsewhere on the board
I2C_A_SDA: U11.36 (SDA); also elsewhere on the board

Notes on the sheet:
HDMI OUT1 I2C bus A, ADV7513 address 0x72 (PD/AD=L)
Unused audio inputs (SPDIF, MCLK, I2S0-3, SCLK, LRCLK) tied to GND. CEC_CLK: 0R to GND (lift to add a 3-100 MHz clock).
Decoupling: place 0.1uF at each supply pin. C_5V_OUT near TPD12S016 pin 13. AVDD/PVDD/BGVDD fed through ferrite beads.
TMDS pairs: 100 ohm differential, length-matched within 0.1 mm per pair, TPD12S016 within 10 mm of the connector.
